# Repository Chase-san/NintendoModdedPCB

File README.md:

# NintendoModdedPCB

Modifications of my remakes various Nintendo PCB with KiCAD. Usually for F-RAM and battery.

These were designed with the help of Mhouranix1125, which created the excellent [DMG-KGDU-10+](https://github.com/Mhouranix1125/DMG-KGDU-10-Plus-FRAM-Upgraded-PCB)

# License

These boards are released under the Creative Commons Attribution 4.0 International License. See the LICENSE for more details. These boards are intended specifically for the modification of official games. There are better boards for creating flash carts.

# Boards

Click the revision to go to that release of the board (gerber files).

| ID            | MOD            | Revision |
| :------------ | :------------- | :------: |
| DMG-A02-MOD   | F-RAM          | [REV2](https://github.com/Chase-san/NintendoModdedPCB/releases/tag/dmg-a02-mod-rev2) |
| DMG-KGDU-MOD2 | F-RAM, BATTERY | [REV2](https://github.com/Chase-san/NintendoModdedPCB/releases/tag/dmg-kgdu-mod2-rev2) |

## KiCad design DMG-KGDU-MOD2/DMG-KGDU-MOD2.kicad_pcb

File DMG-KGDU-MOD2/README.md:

# DMG-KGDU-MOD2

This is an F-RAM and battery holder upgrade to the DMG-KGDU-10.

## Components

This board features a 32-pin ROM and a 28-pin RAM module.

| Ref   | Package     | Description  | Notes | 
| :---: | :---------: | :----------- | :---- |
| U1    | TSOP-II-44W | Program ROM  | ~10.1mm wide |
| U2    | LQFP-32     | MBC-3        | |
| U3    | SOIC-28W    | F-RAM        | ~8.3mm wide |
| U4    | SOIC-8      | System Reset | ~4.3mm wide |
| U5    | SOT-23-5    | Clock Sync   | OR Gate |
| C1,C2 | 0603 (in)   | 15pF Capacitor | |
| C3,C4,C6 | 0603 (in) | 15nF-0.1uF Capacitor | |
| C5    | 0603 (in)   | 33pF Capacitor | May be left empty. |
| R1    | 0603 (in)   | 1kOhm Resistor | |
| R2    | 0603 (in)   | 330kOhm Resistor | |
| X1    | 6mm x 2mm   | 32.768 kHZ Cystal | 12.5 pF Load and 35 kOhm ESR |
| Batt  | CR2025      | Battery Holder | |

It is highly recommended to use the following parts.

| Ref  | Manufacturer | Component |
| :--: | :----------: | :-------: |
| U3   | Infineon     | FM18W08   |
| U5   | Texas Instruments | SN74LVC1G32DBVR |
| Batt | MPD          | BK-6219   |

## Images

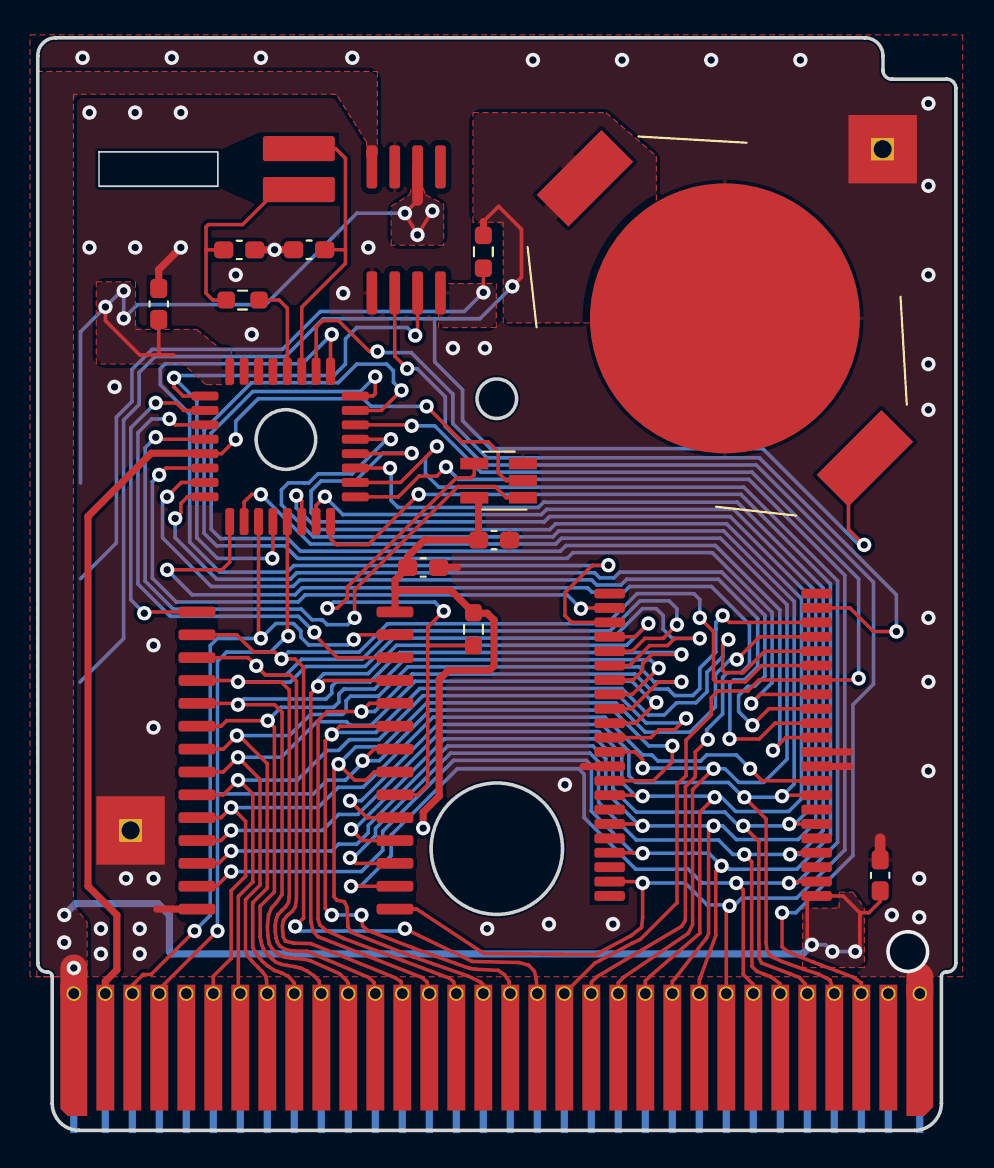
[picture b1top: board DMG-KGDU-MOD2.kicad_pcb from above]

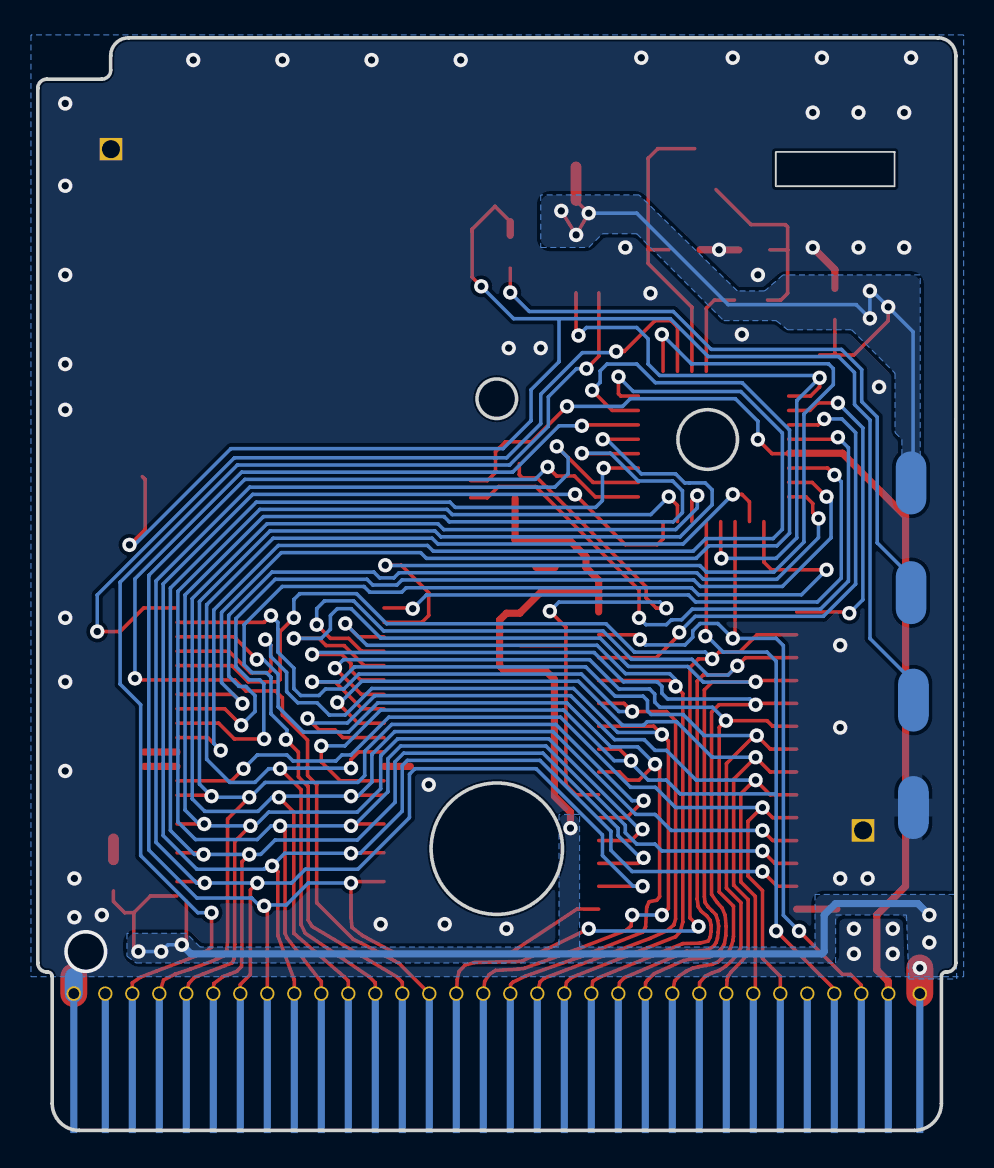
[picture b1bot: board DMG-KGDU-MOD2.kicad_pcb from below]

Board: 2 copper layers, 51.0 x 60.7 mm, 23 parts (4 on the bottom side), 48 nets.

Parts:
BT1: Batt CR2025; BAT-HLD-002
C1, C2: 15pF; C_0603_1608Metric_Pad1.08x0.95mm_HandSolder
C3, C4, C5, C6: 0.1pF; C_0603_1608Metric_Pad1.08x0.95mm_HandSolder
GND1: GroundPad_Square_TH_3.8mm
GND**: GroundPad_Square_TH_3.8mm
R1: 1kΩ; R_0603_1608Metric_Pad0.98x0.95mm_HandSolder
R2: 330kΩ; R_0603_1608Metric_Pad0.98x0.95mm_HandSolder
R3: 10kΩ; R_0603_1608Metric_Pad0.98x0.95mm_HandSolder
TP1, TP2, TP3, TP4: TestPoint_3.5x1.7mm
U0: CartBus; GameBoy_GamePak_CGB-002_P1.50mm_Edge
U1: PRG; TSOP-II-44_MROM
U2: MBC3A; LQFP-32_MBC
U3: RAM; SOIC-28_SRAM
U4: MM1134; SO-8_SYSRST
U5: 74LVC1G32; SOT-23-5_HandSoldering
X1: Crystal_D2mm_L6mm_Horizontal

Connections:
A00: U0.6, U1.31, U3.10
A01: U0.7, U1.11, U3.9
A02: U0.8, U1.10, U3.8
A03: U0.9, U1.9, U3.7
A04: U0.10, U1.8, U3.6
A05: U0.11, U1.7, U3.5
A06: U0.12, U1.6, U3.4
A07: U0.13, U1.5, U3.3
A08: U0.14, U1.4, U3.25
A09: U0.15, U1.42, U3.24
A10: U0.16, U1.41, U3.21
A11: U0.17, U1.40, U3.23
A12: U0.18, U1.39, U3.2
A13: U0.19, U1.38, U2.14
A14: U0.20, U2.1
A15: U0.21, U1.12, U2.2
AA13: U2.27, U3.26
AA14: U2.26, U3.1
BT+: BT1.1, BT1.2, R1.2, TP3.1
CE: R3.1, U3.20, U5.4
Clock: U0.2, U2.29, U5.2
D0: U0.22, U1.15, U2.6, U3.11
D1: U0.23, U1.17, U2.7, U3.12
D2: U0.24, U1.19, U2.8, U3.13
D3: U0.25, U1.21, U2.9, U3.15
D4: U0.26, U1.24, U2.10, U3.16
D5: U0.27, U1.26, U2.11, U3.17
D6: U0.28, U1.28, U2.12, U3.18
D7: U0.29, U1.30, U2.13, U3.19
GND: BT1.3, C1.1, C2.2, C3.2, C4.2, C5.2, C6.2, GND1.1, GND**.1, TP4.1, U0.32, U1.13, U1.32, U1.33, U2.22, U2.23, U3.14, U4.1, U4.7, U5.3
RA14: U1.37, U2.15
RA15: U1.36, U2.32
RA16: U1.35, U2.31
RA17: U1.34, U2.16
RA18: U1.3, U2.17
RA19: U1.2, U2.30
RA20: U1.43, U2.18
RAMCS: U2.28, U5.1
Read: U0.4, U1.14, U2.5, U3.22
Reset: U0.30, U4.2
SYS_RST: U2.4, U2.25, U4.3
VBATT: R1.1, TP2.1, U4.4
VCC: C3.1, C5.1, C6.1, R3.2, U0.1, U1.23, U3.28, U4.8, U5.5
VOUT: C4.1, TP1.1, U2.24, U4.6
Write: U0.3, U2.3, U3.27
XIN: C1.2, U2.19, X1.1
XOUT: R2.2, U2.20
X_: C2.1, R2.1, X1.2

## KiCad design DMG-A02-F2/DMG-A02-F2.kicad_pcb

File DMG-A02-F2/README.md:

# DMG-A02-MOD

This is an F-RAM and battery holder upgrade to the DMG-A02-10. This board is good for Pokemon Red, Blue, and Yellow as well many other games.

## Components

This board features a 32-pin ROM and a 28-pin RAM module.

| Ref   | Package     | Description  | Notes | Part |
| :---: | :---------: | :----------- | :---- | :--- |
| U1    | SSOP-32W    | Program ROM  | | |
| U2    | LQFP-32     | MBC-5        | | |
| U3    | SOIC-28W    | F-RAM        | | |
| U4    | TSOP-6      | Clock Sync   | OR Gate | 74LVC1G332GV,125 |
| C1, C2, C3, C4, C5 | 0603 (in)   |  0.015uF - 0.1uF Capacitor | |
| C6    | 0603 (in)   | 33pF Capacitor | May be left empty | |
| R1    | 0603 (in)   | 10k Ohm Resistor | | |

## Change Log

### REV2 (2023-01-29)
- Added teardrops.

### REV1 (2023-01-21)
- Initial creation.

## Images

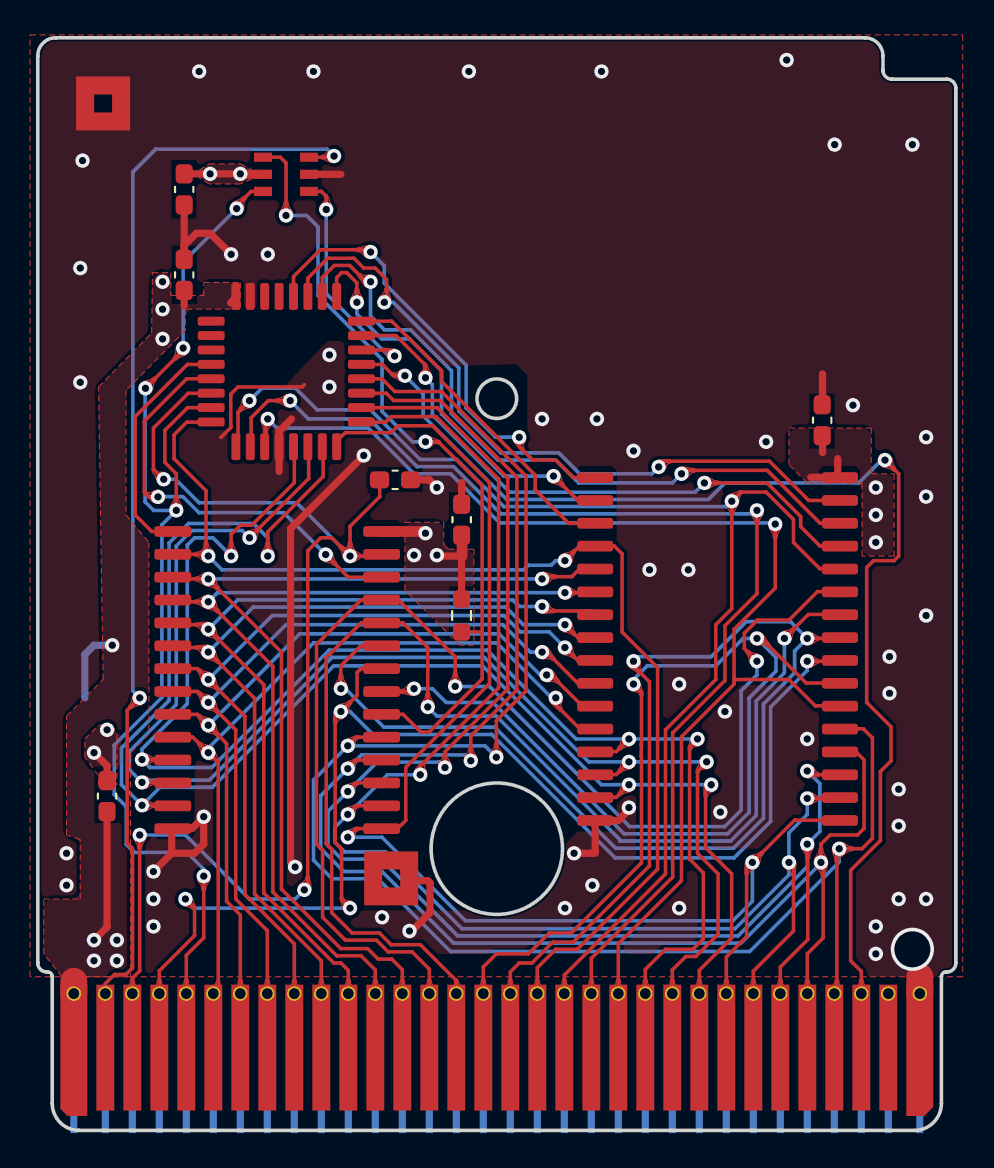
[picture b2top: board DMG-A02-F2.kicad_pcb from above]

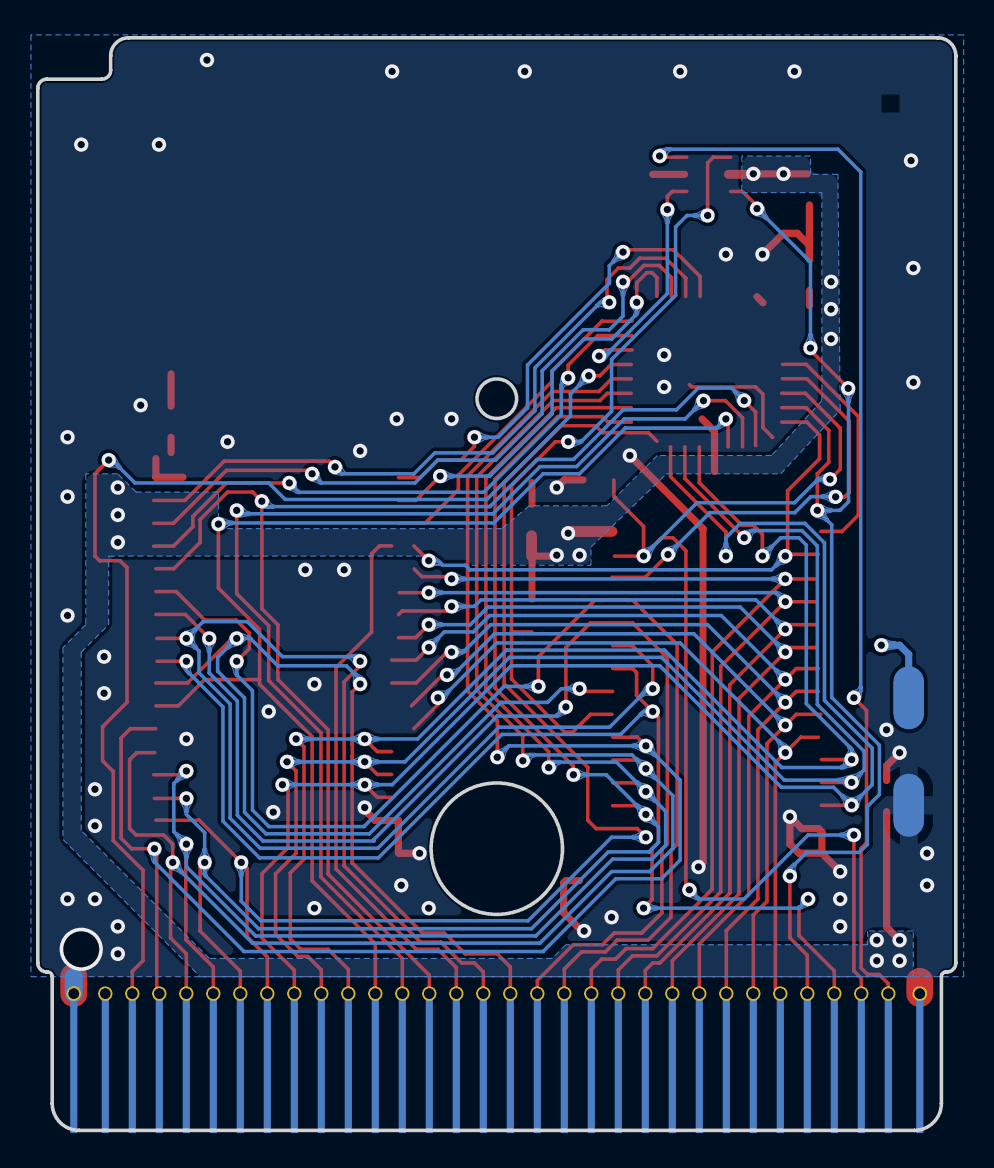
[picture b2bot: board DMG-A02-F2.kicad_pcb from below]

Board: 2 copper layers, 51.0 x 60.7 mm, 16 parts (2 on the bottom side), 41 nets.

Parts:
C1, C2, C3, C4, C5, C6: ?? F; C_0603_1608Metric_Pad1.08x0.95mm_HandSolder
G1, G2: GroundPad_Square_SMD_3mm
GND: TestPoint_3.5x1.7mm
R1: R_0603_1608Metric_Pad0.98x0.95mm_HandSolder
U0: CartBus; GameBoy_GamePak_CGB-002_P1.50mm_Edge
U1: SSOP-32_MROM
U2: LQFP-32_MBC
U3: SOIC-28_SRAM
U4: TSOP-6_1.65x3.05mm_P0.95mm
VCC: TestPoint_3.5x1.7mm

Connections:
A00: U0.6, U1.12, U3.10
A01: U0.7, U1.11, U3.9
A02: U0.8, U1.10, U3.8
A03: U0.9, U1.9, U3.7
A04: U0.10, U1.8, U3.6
A05: U0.11, U1.7, U3.5
A06: U0.12, U1.6, U3.4
A07: U0.13, U1.5, U3.3
A08: U0.14, U1.27, U3.25
A09: U0.15, U1.26, U3.24
A10: U0.16, U1.23, U3.21
A11: U0.17, U1.25, U3.23
A12: U0.18, U1.4, U2.32, U3.2
A13: U0.19, U1.28, U2.1
A14: U0.20, U2.2
A15: U0.21, U1.22, U2.3
CS: U0.5, U2.31, U4.6
Clock: U0.2, U4.3
D0: U0.22, U1.13, U2.5, U3.11
D1: U0.23, U1.14, U2.6, U3.12
D2: U0.24, U1.15, U2.7, U3.13
D3: U0.25, U1.17, U2.8, U3.15
D4: U0.26, U1.18, U2.9, U3.16
D5: U0.27, U1.19, U2.10, U3.17
D6: U0.28, U1.20, U2.11, U3.18
D7: U0.29, U1.21, U2.12, U3.19
GND: C1.2, C2.2, C3.2, C4.2, C5.2, C6.2, G1.1, G2.1, GND.1, U0.32, U1.16, U2.4, U2.23, U3.14, U4.2
OR_A: U2.14, U4.1
OR_Y: R1.1, U3.20, U4.4
RA14: U1.29, U2.15
RA15: U1.3, U2.16
RA16: U1.2, U2.17
RA17: U1.30, U2.18
RA18: U1.31, U2.19
RA19: U1.1, U2.20
Read: U0.4, U1.24, U3.22
Reset: U0.30, U2.13
SA13: U2.29, U3.26
SA14: U2.28, U3.1
VCC: C1.1, C2.1, C3.1, C4.1, C5.1, R1.2, U0.1, U1.32, U2.24, U3.28, U4.5, VCC.1
Write: C6.1, U0.3, U2.30, U3.27

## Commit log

2023-01-21 Modded Boards
2023-01-21 Fix images
2023-01-21 Generate Gerber
2023-01-21 A02-MOD and REV2 KGDU
2023-01-21 Update READMEs
2023-01-22 Fix text placement.
2023-01-29 Update A02 to REV2
2023-01-29 Fixing irrelevant DRC warning.
2023-02-03 Update footprints
2023-02-03 Rename A02-MOD to F2
2023-06-19 Update KGDU BOM.
2023-11-27 Update for new stuff.
2026-05-02 Updated A02 readme

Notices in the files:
DMG-A02-F2/DMG-A02-F2.kicad_pcb:
©1998
DMG-KGDU-MOD2/DMG-KGDU-MOD2.kicad_pcb:
©2000
